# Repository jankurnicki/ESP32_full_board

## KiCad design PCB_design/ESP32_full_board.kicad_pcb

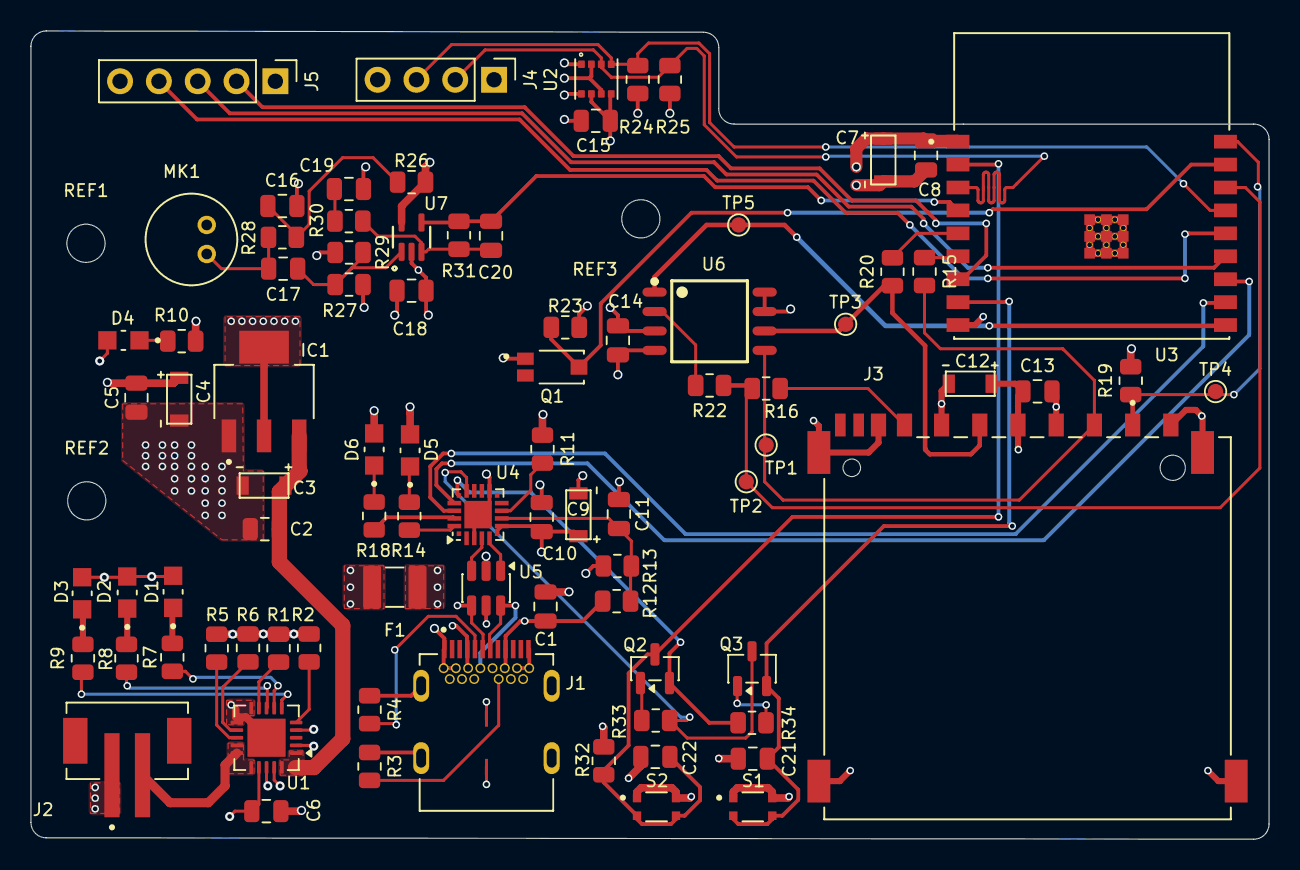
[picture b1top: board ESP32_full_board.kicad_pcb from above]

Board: 4 copper layers, 81.0 x 52.9 mm, 88 parts (0 on the bottom side), 58 nets.

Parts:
C1, C2, C5, C8, C10, C13, C14, C15, C16, C18, C20, C21: 0.1u; C_0805_2012Metric
C3, C4, C7, C12: 10u; T491A106K010AT
C6, C11, C19, C22: 1u; C_0805_2012Metric
C9: 4.7u; T491A106K010AT
C17: 10n; C_0805_2012Metric
D1, D2, D3, D4, D5, D6: LTST-C170GKT; LED_LTST-C170GKT
F1: 0ZCH0110AF2E; FUSC3225X100N
IC1: LM1117MPX-3.3_NOPB; VREG_LM1117MPX-3.3_NOPB
J1: SS-52400-002; BELFUSE_SS-52400-002
J2: B2B-PH-SM4-TB; JST_B2B-PH-SM4-TB
J3: GSD090012SEU; AMPHENOL_GSD090012SEU
J4: Conn_01x04_Pin; PinHeader_1x04_P2.54mm_Vertical
J5: Conn_01x05_Pin; PinHeader_1x05_P2.54mm_Vertical
MK1: CMC-5042PF-AC; CUI_CMC-5042PF-AC
Q1: TEMT6000X01; TRANS_TEMT6000X01
Q2: BC817; SOT-23
Q3: BC817; SOT-23-3
R1, R2, R19, R23, R30, R32, R33, R34: 10K; R_0805_2012Metric
R3, R4: 5k1; R_0805_2012Metric
R5: 2k; R_0805_2012Metric
R6: 20k; R_0805_2012Metric
R7, R8, R9, R10, R14, R18: 470; R_0805_2012Metric
R11: 1K; R_0805_2012Metric
R12: 22K1; R_0805_2012Metric
R13: 47K5; R_0805_2012Metric
R15, R16, R20, R22: 50; R_0805_2012Metric
R24, R25: 4.7k; R_0805_2012Metric
R26, R28: 2K; R_0805_2012Metric
R27, R29: 1M; R_0805_2012Metric
R31: 100K; R_0805_2012Metric
REF1, REF2, REF3: MountingHole_2.5mm
S1: Boot; SW_USLPT2819DT2TR
S2: Reset; SW_USLPT2819DT2TR
TP1: Test MOSI; TestPoint_Pad_D1.0mm
TP2: Test MISO; TestPoint_Pad_D1.0mm
TP3: Test SCLK; TestPoint_Pad_D1.0mm
TP4: Test CS_DS; TestPoint_Pad_D1.0mm
TP5: Test CS; TestPoint_Pad_D1.0mm
U1: MCP73871; QFN-20-1EP_4x4mm_P0.5mm_EP2.5x2.5mm
U2: BME280; PSON65P250X250X100-8N
U3: ESP32-C3-WROOM-02-H4; MODULE_ESP32-C3-WROOM-02-H4
U4: CP2102N-Axx-xQFN20; SiliconLabs_QFN-20-1EP_3x3mm_P0.5mm_EP1.8x1.8mm
U5: USBLC6-2SC6; SOT-23-6
U6: W25Q32JVSSIQ; SOIC127P790X216-8N
U7: MAX4466EXK; SOT65P210X110-5N

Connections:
+3.3V: C4.1, C5.1, C7.1, C8.1, C9.1, C10.2, C12.1, C13.1, C14.1, C15.1, C18.1, D4.2, D5.2, D6.2, IC1.2 (OUTPUT), IC1.4 (VOUT), J3.4 (VDD1), J4.1, J5.1, R11.1, R19.2, R23.1, R24.1, R25.1, R26.1, R27.2, R32.2, U2.2 (CSB), U2.6 (VDDIO), U2.8 (VDD), U3.1 (3V3), U4.6 (VDD), U4.7 (VREGIN), U6.3 (~WP(IO2)), U6.7 (~HOLD/~RESET(IO3)), U6.8 (VCC), U7.5 (VCC)
+5V: C2.1, C3.1, IC1.3 (INPUT), U1.1 (OUT), U1.20 (OUT)
/+5V_USB: C6.1, D1.2, D2.2, D3.2, F1.2, U1.2 (VPCC), U1.4 (PROG2), U1.17 (CE), U1.18 (IN), U1.19 (IN)
/CHARGED: R8.1, U1.8 (STAT1/~LBO)
/CHARGING: R9.1, U1.6 (~PG)
/CHARGING_POWER_GOOD: R7.1, U1.7 (STAT2)
/ESP32-C3-02/BOOT: C21.1, Q3.2 (E), S1.3, S1.4, U3.8 (IO9)
/ESP32-C3-02/CS: TP5.1 (1_1), U3.10 (IO10), U6.1 (~CS)
/ESP32-C3-02/CS_SD: J3.1 (CD/DAT3), R19.1, TP4.1 (1_1), U3.18 (IO0)
/ESP32-C3-02/DTR: Q3.3 (C), R33.1, U4.15 (~CTS)
/ESP32-C3-02/EN: C22.1, Q2.3 (C), R32.1, S2.3, S2.4, U3.2 (EN)
/ESP32-C3-02/GPIO8: J5.2, U3.7 (IO8)
/ESP32-C3-02/GPIO18: J5.3, U3.13 (IO18)
/ESP32-C3-02/GPIO19: J5.4, U3.14 (IO19)
/ESP32-C3-02/MIC_OUT: C20.1, R31.2, U3.4 (IO5), U7.4 (OUT)
/ESP32-C3-02/MISO_DO: R16.2, R22.1, TP2.1 (1_1), U3.16 (IO2)
/ESP32-C3-02/MOSI_DI: J3.2 (CMD), R15.2, TP1.1 (1_1), U6.5 (DI(IO0))
/ESP32-C3-02/PHOTO_C: Q1.3, R23.2, U3.17 (IO1)
/ESP32-C3-02/RTS: Q2.2 (E), R34.1, U4.16 (~RTS)
/ESP32-C3-02/RX_TX: U3.12 (TXD), U4.17 (RXD)
/ESP32-C3-02/SCL: J4.3, R24.2, U2.4 (SCK), U3.15 (IO3)
/ESP32-C3-02/SCLK: J3.5 (CLK), R20.1, TP3.1 (1_1), U6.6 (CLK)
/ESP32-C3-02/SDA: J4.2, R25.2, U2.3 (SDI), U3.3 (IO4)
/ESP32-C3-02/TX_RX: U3.11 (RXD), U4.18 (TXD)
/ESP32-C3-02/USB_D+: U4.4 (D+), U5.3 (I/O2)
/ESP32-C3-02/USB_D-: U4.5 (D-), U5.1 (I/O1)
/USB_DN: J1.A7 (DN1), J1.B7 (DN2), U5.6 (I/O1)
/USB_DP: J1.A6 (DP1), J1.B6 (DP2), U5.4 (I/O2)
/VBAT: J2.2, U1.14 (V_{BAT}), U1.15 (V_{BAT}), U1.16 (V_{BAT_SENSE})
/VBUS: C1.1, F1.1, J1.A4 (VBUSA1), J1.A9 (VBUSA2), J1.B4 (VBUSB1), J1.B9 (VBUSB2), R12.1, U5.5 (VBUS)
GND: C1.2, C2.2, C3.2, C4.2, C5.2, C6.2, C7.2, C8.2, C9.2, C10.1, C11.2, C12.2, C13.2, C14.2, C15.2, C16.2, C18.2, C19.2, C21.2, C22.2, IC1.1 (ADJ/GND), J1.A1 (GNDA1), J1.A12 (GNDA2), J1.B1 (GNDB1), J1.B12 (GNDB2), J1.G1 (GND/SHIELD), J1.G2 (GND/SHIELD), J1.G3 (GND/SHIELD), J1.G4 (GND/SHIELD), J1.S1 (GND/SHIELD), J1.S2 (GND/SHIELD), J1.S3 (GND/SHIELD), J1.S4 (GND/SHIELD), J2.1, J3.3 (VSS1), J3.6 (VSS2), J3.8 (DAT1), J3.9 (DAT2), J3.G1 (SHIELD_GND), J3.G2 (SHIELD_GND), J3.G3 (SHIELD_GND), J3.G4 (SHIELD_GND), J4.4, J5.5, MK1.GND, Q1.1, R1.2, R2.2, R3.1, R4.1, R5.2, R6.2, R10.1, R13.2, R29.2, S1.1, S1.2, S2.1, S2.2, U1.10 (V_{SS}), U1.11 (V_{SS}), U1.21 (V_{SS}), U2.1 (GND), U2.5 (SDO), U2.7 (GND), U3.9 (GND), U3.19 (GND), U3.20 (GND), U3.21 (GND), U3.22 (GND), U3.23 (GND), U3.24 (GND), U3.25 (GND), U3.26 (GND), U3.27 (GND), U3.28 (GND), U3.29 (GND), U3.30 (GND), U3.31 (GND), U3.32 (GND), U3.33 (GND), U3.34 (GND), U3.35 (GND), U3.36 (GND), U3.37 (GND), U3.38 (GND), U3.39 (GND), U4.3 (GND), U4.12 (GND), U4.21 (GND), U5.2 (GND), U6.4 (GND), U7.2 (GND)
unnamed: C16.1, R26.2, R28.1
unnamed: C17.2, MK1.OUT, R28.2
unnamed: C19.1, R30.2
unnamed: D1.1, R7.2
unnamed: D2.1, R8.2
unnamed: D3.1, R9.2
unnamed: D4.1, R10.2
unnamed: D5.1, R14.2
unnamed: D6.1, R18.2
unnamed: J1.A5 (CC1), R4.2
unnamed: J1.B5 (CC2), R3.2
unnamed: J3.7 (DAT0), R16.1
unnamed: Q2.1 (B), R33.2
unnamed: Q3.1 (B), R34.2
unnamed: R5.1, U1.13 (PROG1)
unnamed: R6.1, U1.12 (PROG3)
unnamed: R2.1, U1.5 (THERM)
unnamed: R1.1, U1.9 (~TE)
unnamed: R20.2, U3.5 (IO6)
unnamed: R15.1, U3.6 (IO7)
unnamed: C11.1, R12.2, R13.1, U4.8 (VBUS)
unnamed: R11.2, U4.9 (~RST)
unnamed: R18.1, U4.19 (~RXT/GPIO.3)
unnamed: R14.1, U4.20 (~TXT/GPIO.2)
unnamed: R22.2, U6.2 (DO(IO1))
unnamed: C17.1, R27.1, R29.1, U7.1 (IN+)
unnamed: C20.2, R30.1, R31.1, U7.3 (IN-)
